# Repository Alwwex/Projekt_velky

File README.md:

# LaserPlan – chytrý laserový metr s Bluetooth pro náčrt půdorysu

Nakresli prstem nebo perem obrys místnosti na tabletu, ťukni na stěnu, zmáčkni **MĚŘIT** na laseru –
rozměr se sám zapíše do náčrtu, celý půdorys se přepočítá a aplikace vybere další stěnu.
Stěny, které jde dopočítat, měřit nemusíš. Na konci máš plochu, obvod a export do PNG / SVG / DXF.

| Deska plošného spoje (90 × 44 mm) | Spodní strana | Krabička pro 3D tisk |
|---|---|---|
|  |  |  |

## Co je v projektu

| Část | Kde | Stav |
|---|---|---|
| **Elektronika** – schéma, DPS (KiCad 7), Gerbery, kusovník, osazovací soubor | [`hardware/`](hardware/) | DRC bez chyb, 0 nespojených plošek |
| **Firmware** pro ESP32-C3 (Bluetooth LE, ovladače laser modulů, OLED, tlačítka, baterie) | [`firmware/`](firmware/) | přeloženo (PlatformIO) |
| **Aplikace** pro tablet/telefon/PC (náčrt půdorysu + Web Bluetooth), funguje offline | [`app/`](app/) | testy + E2E test v Chromiu prochází |
| **Krabička** pro 3D tisk (OpenSCAD + STL) | [`hardware/krabicka/`](hardware/krabicka/) | STL připravené |
| **Dokumentace** | [`docs/`](docs/) | |

## Jak to funguje

```mermaid
flowchart LR
  subgraph Přístroj["Laserový metr (ESP32-C3)"]
    L[Laserový modul<br/>UART] -->|vzdálenost| M[ESP32-C3]
    B[Tlačítko MĚŘIT] --> M
    M --> O[OLED displej]
    M --> Z[Bzučák]
    A[Li-Pol 1000 mAh<br/>nabíjení přes USB-C] --> M
  end
  M -- "Bluetooth LE<br/>(měření, stav, příkazy)" --> T
  subgraph T["Tablet / telefon / PC – aplikace v prohlížeči"]
    N[Náčrt perem → rovné stěny 90°/45°] --> S[Výběr stěny]
    S --> R[Přiřazení rozměru + dopočet<br/>uzavřeného obrysu]
    R --> E[Plocha, obvod, export PNG/SVG/DXF]
  end
```

1. **Laserový modul** (průmyslový UART dálkoměr, přesnost ±1–3 mm, dosah 40–100 m) změří vzdálenost.
2. **ESP32-C3** přičte offset podle zvolené reference (zadní / přední hrana krabičky), pípne, ukáže hodnotu
   na OLED a pošle ji přes **Bluetooth LE**.
3. **Aplikace** hodnotu zapíše do vybrané stěny. Náčrt se přeškáluje, „volné“ stěny se dopočítají tak,
   aby se obrys uzavřel, a jednoznačně určené stěny se označí `=` (ty měřit nemusíš).
   Když změříš všechno a obrys nesedí, aplikace ukáže **chybu uzavření** – víš, že je někde chyba.

## Rychlý start

### 1) Vyzkoušej aplikaci hned – bez hardwaru
```bash
cd app && python3 -m http.server 8000
# otevři http://localhost:8000 v Chrome/Edge → Připojit laser → Demo režim
```
Nebo zapni GitHub Pages (Settings → Pages → Source: **GitHub Actions**) – workflow
[`pages.yml`](.github/workflows/pages.yml) aplikaci nasadí na HTTPS adresu a přidá stránku pro nahrání firmwaru.

### 2) Prototyp bez vlastní desky (nejrychlejší cesta k fungujícímu měření)
ESP32-C3 SuperMini + laser modul + nepájivé pole → viz [docs/02-prototyp.md](docs/02-prototyp.md).

### 3) Plná verze s vlastní deskou a krabičkou
1. [Nákupní seznam](docs/01-nakupni-seznam.md) – co koupit a kde
2. [Výroba DPS](docs/03-vyroba-dps.md) – objednání desky (JLCPCB apod.), volitelně i s osazením
3. [Sestavení krok za krokem](docs/04-sestaveni.md) – pájení, oživení, laser, krabička, kalibrace
4. [Firmware](docs/05-firmware.md) – nahrání (i z prohlížeče), ovládání, sériová konzole
5. [Aplikace](docs/06-aplikace.md) – instalace na tablet, práce s náčrtem, export
6. [Bluetooth protokol](docs/07-ble-protokol.md) – pro vlastní aplikace

## Ovládání přístroje

| Tlačítko | Krátký stisk | Dlouhý stisk |
|---|---|---|
| **MĚŘIT** | 1. stisk zapne zaměřovací paprsek, 2. stisk měří | průběžné měření (SCAN) |
| **REŽIM** | reference: zadní ↔ přední hrana | jednotky m ↔ ft-in; 3 s = uspat |

Měřit jde i tlačítkem **MĚŘIT** v aplikaci. Modrá LED bliká = čeká na spojení, svítí = připojeno.
Červená LED = nabíjí se, zelená = nabito.

## Důležité poznámky

- **Hardware je navržený a zkontrolovaný softwarově, ale zatím nebyl fyzicky postaven a odzkoušen.**
  Deska prošla kontrolou DRC a netlist schématu je ověřený proti desce, firmware se přeloží a aplikace
  je otestovaná – první kus ale ber jako prototyp. Postup oživení s kontrolami je v [sestavení](docs/04-sestaveni.md).
- **Laserové moduly** se liší protokolem. Firmware umí binární protokol JRT a textový „D/O/C“
  protokol (automatická detekce) + simulaci. Před nákupem si ověř, že modul má **UART s logikou 3,3 V**.
- **iPad/iPhone**: Safari neumí Web Bluetooth – použij prohlížeč **Bluefy** (zdarma v App Store).
  Android, Windows, macOS, Linux a ChromeOS fungují v Chrome/Edge.
- **Li-Pol baterie**: zkontroluj polaritu konektoru (u čínských článků bývá opačně) – viz sestavení.

## Struktura repozitáře

```
app/                 webová aplikace (PWA, bez závislostí) + testy
firmware/            PlatformIO projekt pro ESP32-C3
hardware/
  generator/         Python skripty: zapojení → schéma → DPS → autorouter → výrobní data
  kicad/             KiCad 7 projekt (schéma, deska, knihovna symbolů)
  vyroba/            Gerbery (zip), BOM, CPL, schéma PDF, 3D model STEP
  krabicka/          OpenSCAD model + STL
docs/                návody a obrázky
```

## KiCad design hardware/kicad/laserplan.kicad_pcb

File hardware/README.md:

# Hardware LaserPlan

## Zapojení v kostce

| Blok | Součástky | Poznámka |
|---|---|---|
| USB-C | J1, R1/R2 (5,1 kΩ CC), U1 USBLC6-2SC6 | nabíjení + programování (nativní USB ESP32-C3), ESD ochrana |
| Nabíječka | U2 MCP73831 (≈ 450 mA, R3 2,2 kΩ), D2/D3 LED | červená = nabíjí, zelená = nabito |
| Napájecí cesta | D1 B5819W, Q1 AO3401A, R6 | z USB napájí systém přes diodu, baterie se automaticky odpojí (load sharing) |
| Vypínač, LDO | SW1, U3 AP2112K-3.3 (600 mA) | vypínač odpojí vše kromě nabíjení |
| Měření | R11/R12 (baterie → IO0), R13/R14 (USB → IO1) | |
| MCU | U4 ESP32-C3-WROOM-02 | anténa na hraně desky nad oblastí bez mědi |
| Laser | J2, Q2 AO3401A + Q3 AO3400A, JP1 | spínané napájení modulu s měkkým startem (C10), volba 3,3 V / baterie |
| Ovládání | SW2 MĚŘIT (= BOOT), SW3 REŽIM, D5 modrá LED, BZ1 + Q4 | |
| Displej | J3 – OLED SSD1306 I2C | |

### Piny ESP32-C3

| GPIO | Funkce | GPIO | Funkce |
|---|---|---|---|
| IO0 | ADC baterie | IO6 | I2C SCL |
| IO1 | detekce USB | IO7 | modrá LED |
| IO2 | laser AUX (strap, pull-up) | IO8 | strap (pull-up) |
| IO3 | laser EN | IO9 | MĚŘIT / BOOT |
| IO4 | REŽIM (probouzí ze spánku) | IO10 | bzučák |
| IO5 | I2C SDA | IO20 / IO21 | UART RX ← laser TX / TX → laser RX |
| IO18 / IO19 | USB D− / D+ | | |

## Jak návrh vznikl a jak ho upravit

Celý hardware je **generovaný z kódu** – jediným zdrojem pravdy je
[`generator/circuit.py`](generator/circuit.py) (součástky, hodnoty, pouzdra, sítě).

```bash
cd hardware/generator
./build_all.sh
```

| Skript | Co dělá |
|---|---|
| `gen_schematic.py` | schéma KiCad (`kicad/laserplan.kicad_sch`) – bloky, jmenovky sítí, vlastní symbol ESP32-C3-WROOM-02 |
| `gen_pcb.py place` | deska: footprinty z knihoven KiCadu, rozmístění (`PLACEMENT`), obrys, sítotisk |
| `router.py` | vlastní dvouvrstvý autorouter (A* na mřížce 0,25 mm s přesnou kontrolou izolací, rip-up & reroute, pevně navržené vyvedení USB-C) |
| `gen_pcb.py finish` | rozlitá zem na obou vrstvách, prošívací prokovy, DRC report |
| `export.py` | Gerbery, vrtání, BOM, CPL, PDF schéma, náhledy, STEP |

Potřebuješ **KiCad 7** (s Python modulem `pcbnew`), Python 3 s `numpy` a `cairosvg`.

Kontroly:
- `kicad/drc_report.txt` – **0 chyb, 0 nespojených plošek**. Jediná zbylá upozornění jsou
  `lib_footprint_issues` – vznikají jen proto, že v generovacím prostředí nebyla nastavená globální
  tabulka knihoven footprintů; v normálně nainstalovaném KiCadu zmizí.
- Netlist exportovaný ze schématu (`kicad-cli sch export netlist`) se shoduje s `circuit.py` (34 sítí).

> Pokud budeš desku dál upravovat ručně v KiCadu, už ji negeneruj skripty znovu (přepsaly by tvé změny).
> Schéma a deska jsou propojené (stejná UUID), takže *Aktualizovat DPS ze schématu* funguje.

## Rozměry

- DPS 90 × 44 mm, otvory M2.5 ve vzdálenosti 3,2 mm od rohů
- výška součástek nad DPS: tlačítka 13 mm, OLED na dutinkové liště ≈ 13,7 mm, bzučák 9,5 mm
- pod DPS jen vývody THT součástek (≈ 2 mm)
- krabička: 95 × 52 × 36 mm ([`krabicka/krabicka.scad`](krabicka/krabicka.scad))

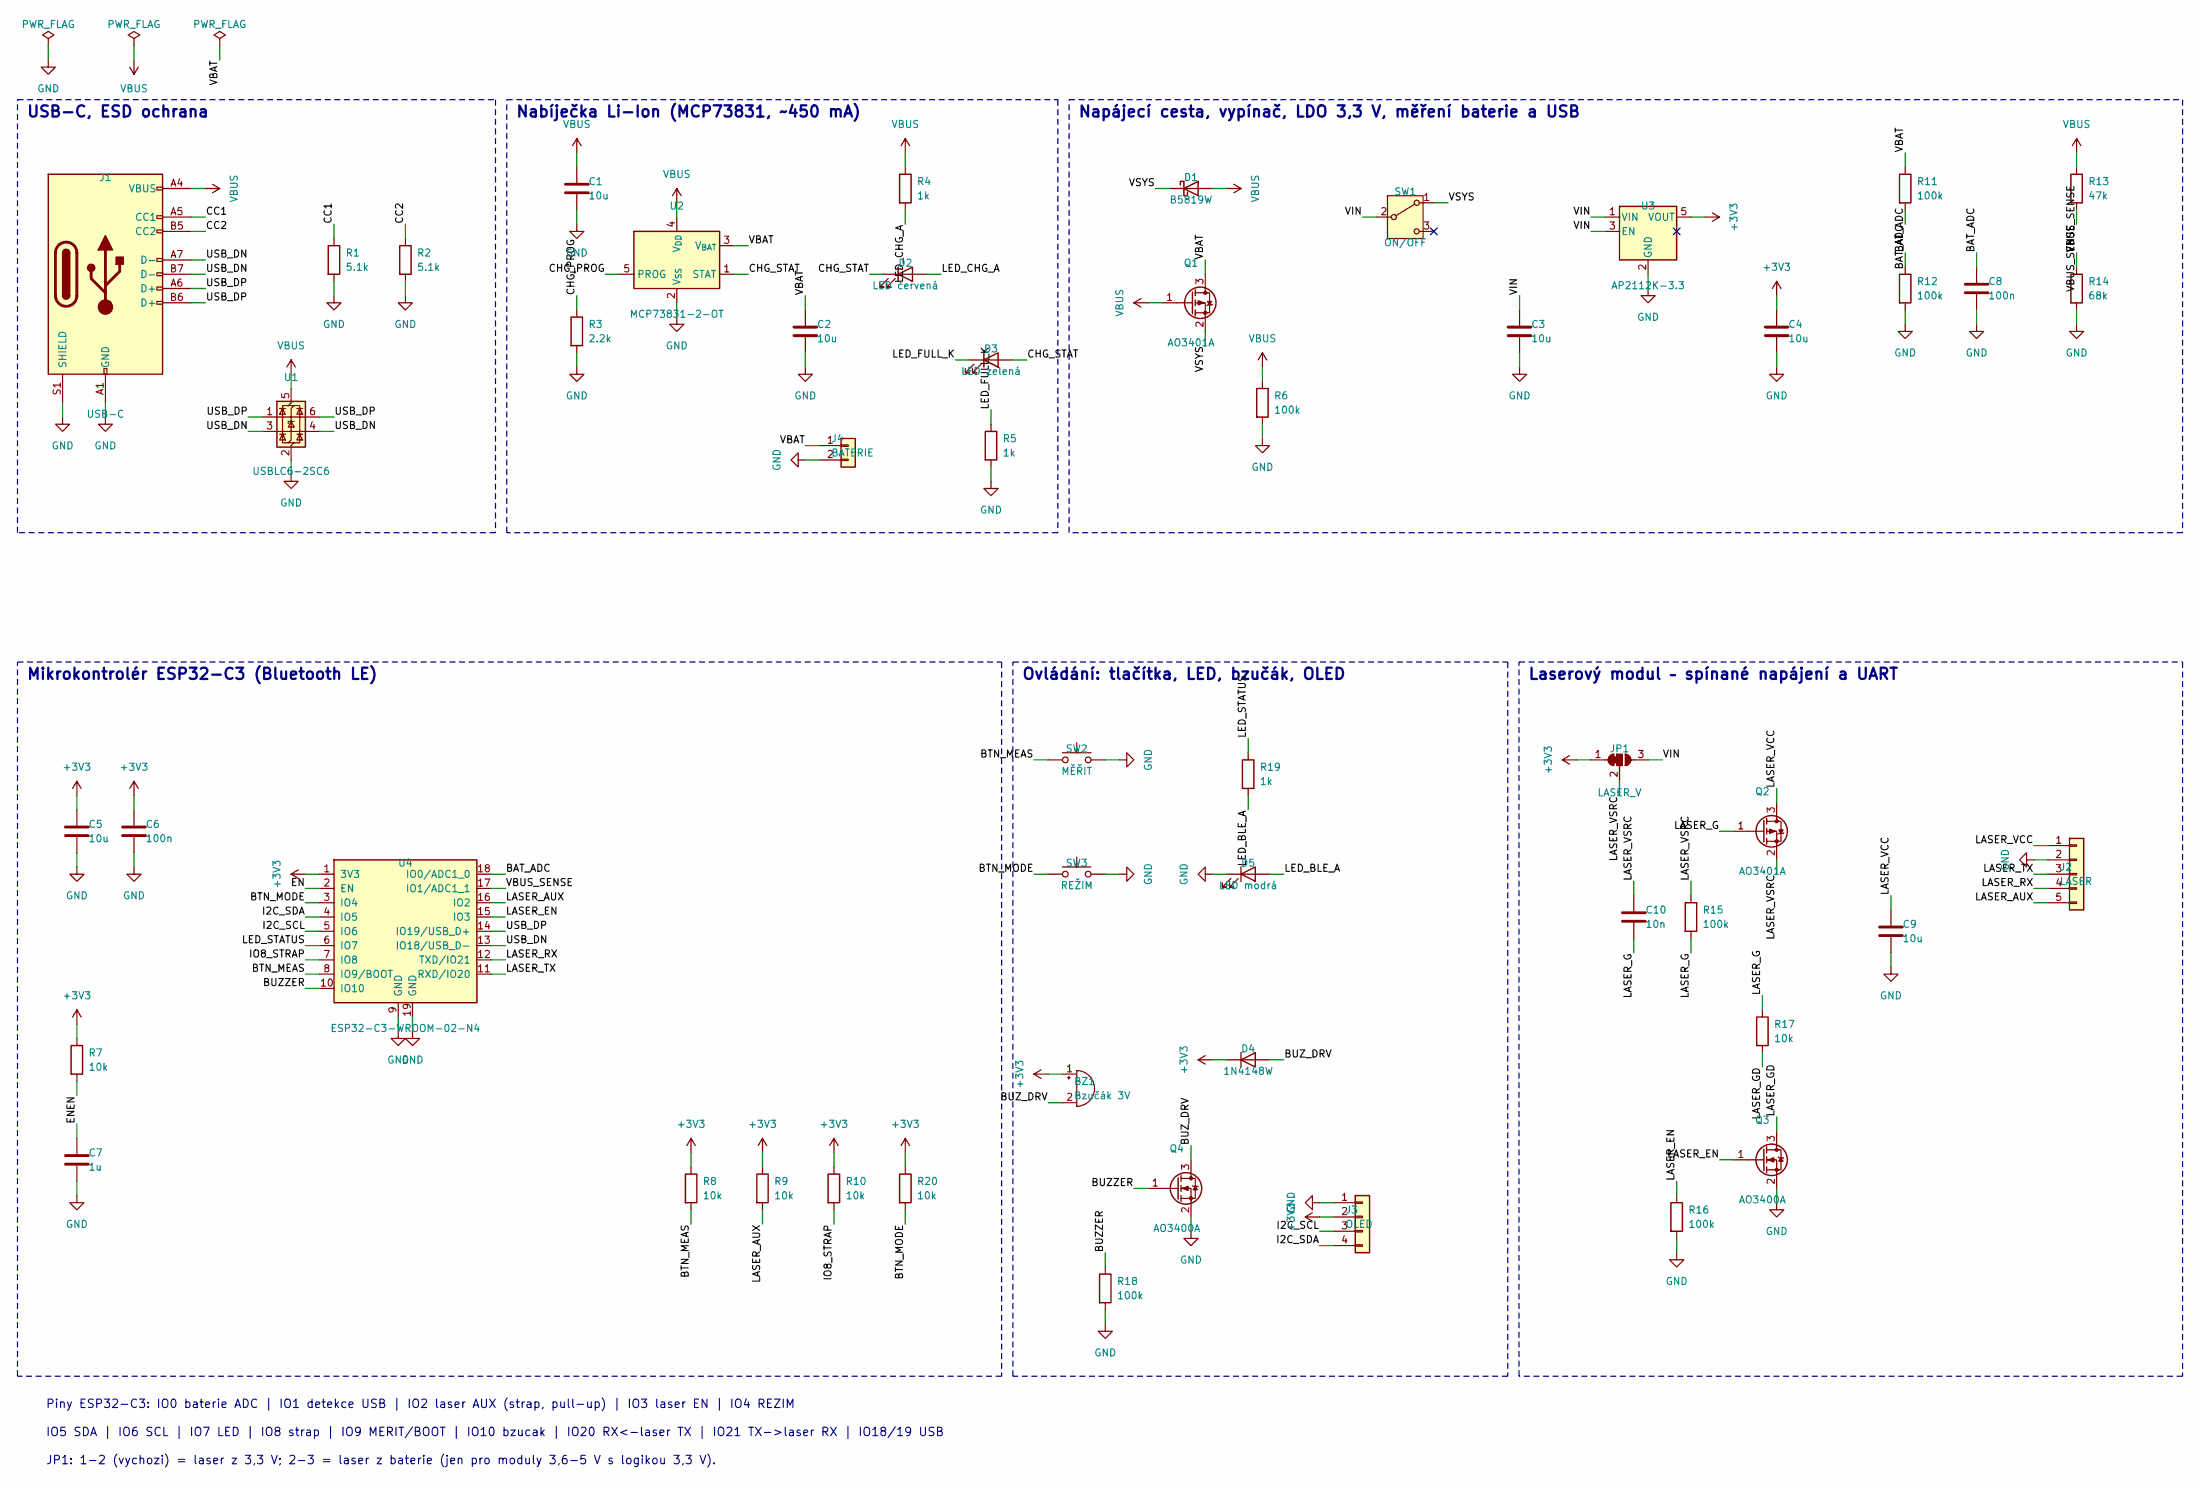
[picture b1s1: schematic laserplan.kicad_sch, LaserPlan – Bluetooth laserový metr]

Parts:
BZ1: Bzučák 3V; Buzzer_12x9.5RM7.6; MPN Pasivní magnetický bzučák 12×9,5 mm, 3 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
C1, C2, C3, C4, C5, C9: 10u; C_0805_2012Metric; MPN 0805 10u X5R/X7R ≥10V
C6, C8: 100n; C_0805_2012Metric; MPN 0805 100n X5R/X7R ≥10V
C7: 1u; C_0805_2012Metric; MPN 0805 1u X5R/X7R ≥10V
C10: 10n; C_0805_2012Metric; MPN 0805 10n X5R/X7R ≥10V
D1: B5819W; D_SOD-123; MPN B5819W
D2: LED červená; LED_0805_2012Metric; MPN LED 0805 červená
D3: LED zelená; LED_0805_2012Metric; MPN LED 0805 zelená
D4: 1N4148W; D_SOD-123; MPN 1N4148W
D5: LED modrá; LED_0805_2012Metric; MPN LED 0805 modrá
J1: USB-C; USB_C_Receptacle_HRO_TYPE-C-31-M-12; MPN TYPE-C-31-M-12
J2: LASER; PinHeader_1x05_P2.54mm_Vertical; MPN Kolíková lišta 1×5, 2,54 mm
J3: OLED; PinSocket_1x04_P2.54mm_Vertical; MPN Dutinková lišta 1×4, 2,54 mm
J4: BATERIE; JST_PH_B2B-PH-K_1x02_P2.00mm_Vertical; MPN B2B-PH-K-S
JP1: LASER_V; SolderJumper-3_P1.3mm_Bridged12_RoundedPad1.0x1.5mm; MPN (pájecí propojka na DPS)
Q1, Q2: AO3401A; SOT-23; MPN AO3401A
Q3, Q4: AO3400A; SOT-23; MPN AO3400A
R1, R2: 5.1k; R_0805_2012Metric; MPN 0805 5.1k 1%
R3: 2.2k; R_0805_2012Metric; MPN 0805 2.2k 1%
R4, R5, R19: 1k; R_0805_2012Metric; MPN 0805 1k 1%
R6, R11, R12, R15, R16, R18: 100k; R_0805_2012Metric; MPN 0805 100k 1%
R7, R8, R9, R10, R17, R20: 10k; R_0805_2012Metric; MPN 0805 10k 1%
R13: 47k; R_0805_2012Metric; MPN 0805 47k 1%
R14: 68k; R_0805_2012Metric; MPN 0805 68k 1%
SW1: ON/OFF; SW_Slide_SPDT_Angled_CK_OS102011MA1Q; MPN OS102011MA1QN1
SW2: MĚŘIT; SW_PUSH_6mm_H13mm; MPN TS-1187A / B3F-1070 (6×6 mm, výška 13 m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
SW3: REŽIM; SW_PUSH_6mm_H13mm; MPN TS-1187A / B3F-1070 (6×6 mm, výška 13 m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
U1: USBLC6-2SC6; SOT-23-6; MPN USBLC6-2SC6
U2: MCP73831-2-OT; SOT-23-5; MPN MCP73831T-2ACI/OT
U3: AP2112K-3.3; SOT-23-5; MPN AP2112K-3.3TRG1
U4: ESP32-C3-WROOM-02-N4; ESP32-C3-WROOM-02; MPN ESP32-C3-WROOM-02-N4

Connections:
+3V3: BZ1.1 (+), C4.1, C5.1, C6.1, D4.1 (K), J3.2, JP1.1 (A), R7.1, R8.1, R9.1, R10.1, R20.1, U3.5 (VOUT), U4.1 (3V3)
BAT_ADC: C8.1, R11.2, R12.1, U4.18 (IO0/ADC1_0)
BTN_MEAS: R8.2, SW2.1, U4.8 (IO9/BOOT)
BTN_MODE: R20.2, SW3.1, U4.3 (IO4)
BUZZER: Q4.1 (G), R18.1, U4.10 (IO10)
BUZ_DRV: BZ1.2 (-), D4.2 (A), Q4.3 (D)
CC1: J1.A5 (CC1), R1.1
CC2: J1.B5 (CC2), R2.1
CHG_PROG: R3.1, U2.5 (PROG)
CHG_STAT: D2.1 (K), D3.2 (A), U2.1 (STAT)
EN: C7.1, R7.2, U4.2 (EN)
GND: C1.2, C2.2, C3.2, C4.2, C5.2, C6.2, C7.2, C8.2, C9.2, D5.1 (K), J1.A1 (GND), J1.A12 (GND), J1.B1 (GND), J1.B12 (GND), J1.S1 (SHIELD), J2.2, J3.1, J4.2, Q3.2 (S), Q4.2 (S), R1.2, R2.2, R3.2, R5.2, R6.2, R12.2, R14.2, R16.2, R18.2, SW2.2, SW3.2, U1.2 (GND), U2.2 (V_{SS}), U3.2 (GND), U4.9 (GND), U4.19 (GND)
I2C_SCL: J3.3, U4.5 (IO6)
I2C_SDA: J3.4, U4.4 (IO5)
IO8_STRAP: R10.2, U4.7 (IO8)
LASER_AUX: J2.5, R9.2, U4.16 (IO2)
LASER_EN: Q3.1 (G), R16.1, U4.15 (IO3)
LASER_G: C10.2, Q2.1 (G), R15.2, R17.1
LASER_GD: Q3.3 (D), R17.2
LASER_RX: J2.4, U4.12 (TXD/IO21)
LASER_TX: J2.3, U4.11 (RXD/IO20)
LASER_VCC: C9.1, J2.1, Q2.3 (D)
LASER_VSRC: C10.1, JP1.2 (C), Q2.2 (S), R15.1
LED_BLE_A: D5.2 (A), R19.2
LED_CHG_A: D2.2 (A), R4.2
LED_FULL_K: D3.1 (K), R5.1
LED_STATUS: R19.1, U4.6 (IO7)
USB_DN: J1.A7 (D-), J1.B7 (D-), U1.3 (I/O2), U1.4 (I/O2), U4.13 (IO18/USB_D-)
USB_DP: J1.A6 (D+), J1.B6 (D+), U1.1 (I/O1), U1.6 (I/O1), U4.14 (IO19/USB_D+)
VBAT: C2.1, J4.1, Q1.3 (D), R11.1, U2.3 (V_{BAT})
VBUS: C1.1, D1.2 (A), J1.A4 (VBUS), J1.A9 (VBUS), J1.B4 (VBUS), J1.B9 (VBUS), Q1.1 (G), R4.1, R6.1, R13.1, U1.5 (VBUS), U2.4 (V_{DD})
VBUS_SENSE: R13.2, R14.1, U4.17 (IO1/ADC1_1)
VIN: C3.1, JP1.3 (B), SW1.2 (B), U3.1 (VIN), U3.3 (EN)
VSYS: D1.1 (K), Q1.2 (S), SW1.1 (A)

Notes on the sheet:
USB-C, ESD ochrana
Nabíječka Li-Ion (MCP73831, ~450 mA)
Napájecí cesta, vypínač, LDO 3,3 V, měření baterie a USB
Mikrokontrolér ESP32-C3 (Bluetooth LE)
Ovládání: tlačítka, LED, bzučák, OLED
Laserový modul – spínané napájení a UART
Piny ESP32-C3: IO0 baterie ADC | IO1 detekce USB | IO2 laser AUX (strap, pull-up) | IO3 laser EN | IO4 REZIM
IO5 SDA | IO6 SCL | IO7 LED | IO8 strap | IO9 MERIT/BOOT | IO10 bzucak | IO20 RX<-laser TX | IO21 TX->laser RX | IO18/19 USB
JP1: 1-2 (vychozi) = laser z 3,3 V; 2-3 = laser z baterie (jen pro moduly 3,6-5 V s logikou 3,3 V).

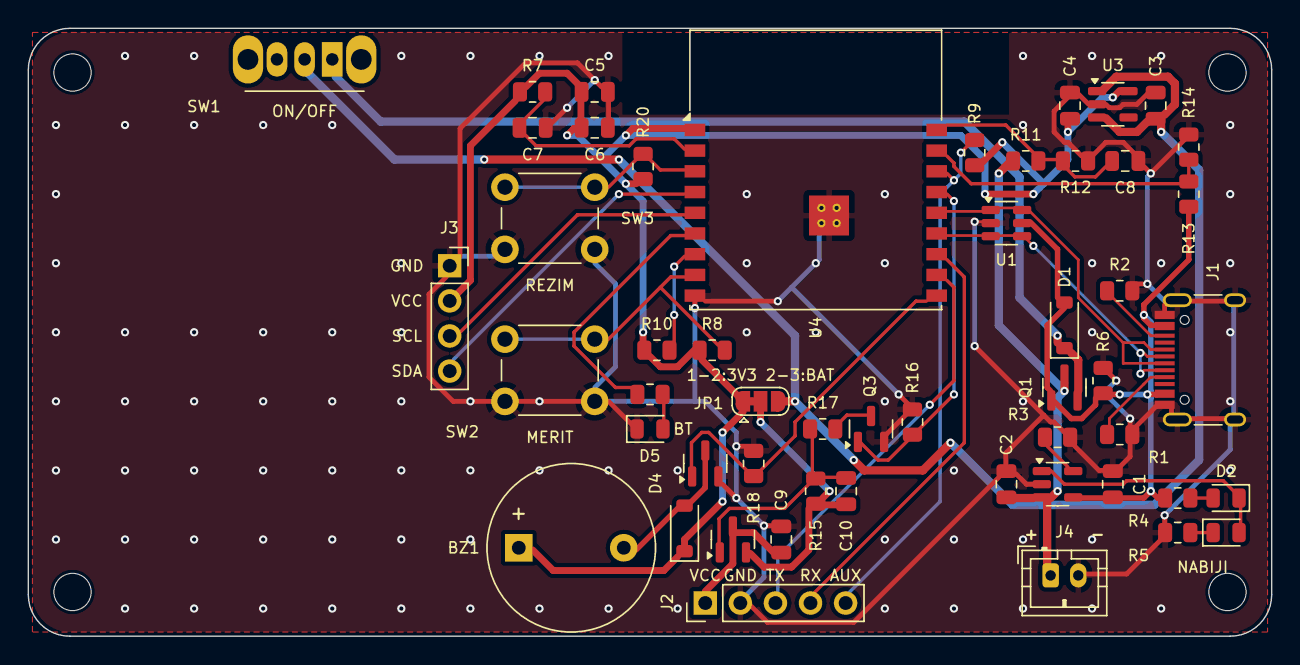
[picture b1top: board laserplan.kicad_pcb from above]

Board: 2 copper layers, 90.0 x 44.0 mm, 56 parts (0 on the bottom side), 34 nets.

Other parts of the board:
H1, H2, H3, H4: M2.5; MountingHole_2.7mm_M2.5

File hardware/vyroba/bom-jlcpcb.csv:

Comment,Designator,Footprint,LCSC Part #,MPN
10u,"C1,C2,C3,C4,C5,C9",C_0805_2012Metric,,0805 10u X5R/X7R ≥10V
10n,C10,C_0805_2012Metric,,0805 10n X5R/X7R ≥10V
100n,"C6,C8",C_0805_2012Metric,,0805 100n X5R/X7R ≥10V
1u,C7,C_0805_2012Metric,,0805 1u X5R/X7R ≥10V
B5819W,D1,D_SOD-123,,B5819W
LED červená,D2,LED_0805_2012Metric,,LED 0805 červená
LED zelená,D3,LED_0805_2012Metric,,LED 0805 zelená
1N4148W,D4,D_SOD-123,,1N4148W
LED modrá,D5,LED_0805_2012Metric,,LED 0805 modrá
USB-C,J1,USB_C_Receptacle_HRO_TYPE-C-31-M-12,,TYPE-C-31-M-12
AO3401A,"Q1,Q2",SOT-23,,AO3401A
AO3400A,"Q3,Q4",SOT-23,,AO3400A
5.1k,"R1,R2",R_0805_2012Metric,,0805 5.1k 1%
47k,R13,R_0805_2012Metric,,0805 47k 1%
68k,R14,R_0805_2012Metric,,0805 68k 1%
2.2k,R3,R_0805_2012Metric,,0805 2.2k 1%
1k,"R4,R5,R19",R_0805_2012Metric,,0805 1k 1%
100k,"R6,R11,R12,R15,R16,R18",R_0805_2012Metric,,0805 100k 1%
10k,"R7,R8,R9,R10,R17,R20",R_0805_2012Metric,,0805 10k 1%
USBLC6-2SC6,U1,SOT-23-6,,USBLC6-2SC6
MCP73831-2-OT,U2,SOT-23-5,,MCP73831T-2ACI/OT
AP2112K-3.3,U3,SOT-23-5,,AP2112K-3.3TRG1
ESP32-C3-WROOM-02-N4,U4,ESP32-C3-WROOM-02,,ESP32-C3-WROOM-02-N4

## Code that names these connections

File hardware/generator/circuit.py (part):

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    dict(ref="U1", symbol="Power_Protection:USBLC6-2SC6", value="USBLC6-2SC6",
         footprint=SOT236, manufacturer="STMicroelectronics", mpn="USBLC6-2SC6",
         desc="ESD ochrana USB datových linek", block="usb", smd=True,
         pins={"1": "USB_DP", "6": "USB_DP", "3": "USB_DN", "4": "USB_DN",
               "2": "GND", "5": "VBUS"}),

    # ---------------------------------------------------------------- nabíječka Li-Ion
    dict(ref="U2", symbol="Battery_Management:MCP73831-2-OT", value="MCP73831-2-OT",
         footprint=SOT235, manufacturer="Microchip", mpn="MCP73831T-2ACI/OT",
         desc="Nabíječka 1článku Li-Ion/LiPo 4,2 V", block="charger", smd=True,
         pins={"1": "CHG_STAT", "2": "GND", "3": "VBAT", "4": "VBUS", "5": "CHG_PROG"}),
    R("R3", "2.2k", "CHG_PROG", "GND", "charger", "Nabíjecí proud ≈ 450 mA (1000/R)"),
    C("C1", "10u", "VBUS", "GND", "charger", "Vstupní kondenzátor nabíječky"),
    C("C2", "10u", "VBAT", "GND", "charger", "Výstupní kondenzátor nabíječky"),
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    dict(ref="D1", symbol="Device:D_Schottky", value="B5819W",
         footprint=SOD123, manufacturer="Diodes / SL", mpn="B5819W",
         desc="Schottky – napájení z USB", block="power", smd=True,
         pins={"1": "VSYS", "2": "VBUS"}),           # 1 = K, 2 = A
    dict(ref="Q1", symbol="Transistor_FET:AO3401A", value="AO3401A",
         footprint=SOT23, manufacturer="Alpha & Omega", mpn="AO3401A",
         desc="P-MOSFET – přepínání baterie/USB (load sharing)", block="power", smd=True,
         pins={"1": "VBUS", "2": "VSYS", "3": "VBAT"}),  # G, S, D
    R("R6", "100k", "VBUS", "GND", "power", "Stahuje gate Q1 bez USB"),
    dict(ref="SW1", symbol="Switch:SW_SPDT", value="ON/OFF",
         footprint="Button_Switch_THT:SW_Slide_SPDT_Angled_CK_OS102011MA1Q",
         manufacturer="C&K", mpn="OS102011MA1QN1",
         desc="Hlavní vypínač (posuvný, úhlový – ovládá se z boku krabičky)", block="power", smd=False,
         pins={"1": "VSYS", "2": "VIN", "3": "NC_SW1"}),
    C("C3", "10u", "VIN", "GND", "power", "Vstup LDO"),
    dict(ref="U3", symbol="Regulator_Linear:AP2112K-3.3", value="AP2112K-3.3",
         footprint=SOT235, manufacturer="Diodes Inc.", mpn="AP2112K-3.3TRG1",
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         # IO4 REŽIM | IO5 SDA | IO6 SCL | IO7 LED | IO8 strap | IO9 MĚŘIT/BOOT
         # IO10 bzučák | IO20 RX<-laser | IO21 TX->laser | IO18/19 USB
         # IO3 laser EN | IO2 laser AUX | IO1 detekce USB | IO0 baterie (ADC)
         pins={"1": "+3V3", "2": "EN", "3": "BTN_MODE", "4": "I2C_SDA",
               "5": "I2C_SCL", "6": "LED_STATUS", "7": "IO8_STRAP", "8": "BTN_MEAS",
               "9": "GND", "10": "BUZZER", "11": "LASER_TX", "12": "LASER_RX",
               "13": "USB_DN", "14": "USB_DP", "15": "LASER_EN", "16": "LASER_AUX",
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         footprint="Button_Switch_THT:SW_PUSH_6mm_H13mm", manufacturer="XKB / Omron",
         mpn="TS-1187A / B3F-1070 (6×6 mm, výška 13 mm)",
         desc="Tlačítko MĚŘIT (zároveň BOOT)", block="ui", smd=False,
         pins={"1": "BTN_MEAS", "2": "GND"}),
    dict(ref="SW3", symbol="Switch:SW_Push", value="REŽIM",
         footprint="Button_Switch_THT:SW_PUSH_6mm_H13mm", manufacturer="XKB / Omron",
         mpn="TS-1187A / B3F-1070 (6×6 mm, výška 13 mm)",
         desc="Tlačítko REŽIM / laser zap", block="ui", smd=False,
         pins={"1": "BTN_MODE", "2": "GND"}),
    R("R19", "1k", "LED_STATUS", "LED_BLE_A", "ui", "Rezistor stavové LED"),
    LED("D5", "modrá", "LED_BLE_A", "GND", "ui", "Stav Bluetooth"),

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         footprint="Buzzer_Beeper:Buzzer_12x9.5RM7.6", manufacturer="Generic",
         mpn="Pasivní magnetický bzučák 12×9,5 mm, 3 V (např. HYT-1205)",
         desc="Akustická signalizace měření", block="ui", smd=False,
         pins={"1": "+3V3", "2": "BUZ_DRV"}),
    dict(ref="Q4", symbol="Transistor_FET:AO3400A", value="AO3400A",
         footprint=SOT23, manufacturer="Alpha & Omega", mpn="AO3400A",
         desc="Spínač bzučáku", block="ui", smd=True,
         pins={"1": "BUZZER", "2": "GND", "3": "BUZ_DRV"}),
    R("R18", "100k", "BUZZER", "GND", "ui", "Gate pull-down"),
    dict(ref="D4", symbol="Device:D", value="1N4148W",
         footprint=SOD123, manufacturer="Diodes / SL", mpn="1N4148W",
         desc="Ochranná dioda bzučáku", block="ui", smd=True,
         pins={"1": "+3V3", "2": "BUZ_DRV"}),         # K, A

    # ---------------------------------------------------------------- laser modul
    dict(ref="JP1", symbol="Jumper:SolderJumper_3_Bridged12", value="LASER_V",
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         manufacturer="-", mpn="(pájecí propojka na DPS)",
         desc="Volba napájení laseru: 1-2 = 3,3 V (výchozí), 2-3 = baterie", block="laser",
         smd=True, no_bom=True,
         pins={"1": "+3V3", "2": "LASER_VSRC", "3": "VIN"}),
    dict(ref="Q2", symbol="Transistor_FET:AO3401A", value="AO3401A",
         footprint=SOT23, manufacturer="Alpha & Omega", mpn="AO3401A",
         desc="Spínač napájení laser modulu", block="laser", smd=True,
         pins={"1": "LASER_G", "2": "LASER_VSRC", "3": "LASER_VCC"}),
    R("R15", "100k", "LASER_VSRC", "LASER_G", "laser", "Gate pull-up (laser vyp.)"),
    C("C10", "10n", "LASER_VSRC", "LASER_G", "laser", "Měkký start laseru"),
    R("R17", "10k", "LASER_G", "LASER_GD", "laser", "Omezení rychlosti sepnutí"),
    dict(ref="Q3", symbol="Transistor_FET:AO3400A", value="AO3400A",
         footprint=SOT23, manufacturer="Alpha & Omega", mpn="AO3400A",
         desc="Budič spínače laseru", block="laser", smd=True,
         pins={"1": "LASER_EN", "2": "GND", "3": "LASER_GD"}),
    R("R16", "100k", "LASER_EN", "GND", "laser", "Laser vypnutý po resetu"),
    C("C9", "10u", "LASER_VCC", "GND", "laser", "Blokování napájení laseru"),
    dict(ref="J2", symbol="Connector_Generic:Conn_01x05", value="LASER",
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         manufacturer="Generic", mpn="Kolíková lišta 1×5, 2,54 mm",
         desc="Laser modul: 1 VCC, 2 GND, 3 TX modulu, 4 RX modulu, 5 AUX", block="laser",
         smd=False,
         pins={"1": "LASER_VCC", "2": "GND", "3": "LASER_TX", "4": "LASER_RX", "5": "LASER_AUX"}),

    # ---------------------------------------------------------------- displej
    dict(ref="J3", symbol="Connector_Generic:Conn_01x04", value="OLED",
         footprint="Connector_PinSocket_2.54mm:PinSocket_1x04_P2.54mm_Vertical",
         manufacturer="Generic", mpn="Dutinková lišta 1×4, 2,54 mm",
         desc="OLED 0,96\" SSD1306 I2C: GND, VCC, SCL, SDA", block="ui", smd=False,
         pins={"1": "GND", "2": "+3V3", "3": "I2C_SCL", "4": "I2C_SDA"}),
]

# Díry pro šrouby M2.5 (jen na DPS, ne ve schématu)
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
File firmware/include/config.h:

#pragma once
// ============================================================================
//  LaserPlan – konfigurace pinů a výchozích hodnot
// ============================================================================
#include <Arduino.h>

#define LP_FW_VERSION "1.0.0"
#define LP_MODEL      "LaserPlan BLE"

// ---------------------------------------------------------------- piny
// Stejné zapojení platí pro vlastní DPS i pro ESP32-C3 SuperMini/DevKitM-1.
static constexpr int PIN_BAT_ADC    = 0;   // dělič 100k/100k z baterie (ADC1_CH0)
static constexpr int PIN_VBUS_SENSE = 1;   // dělič 47k/68k z USB 5 V
static constexpr int PIN_LASER_AUX  = 2;   // volitelný pin modulu (PWR/EN), strap – pull-up
static constexpr int PIN_LASER_EN   = 3;   // 1 = napájení laser modulu zapnuto
static constexpr int PIN_BTN_MODE   = 4;   // tlačítko REŽIM (aktivní v nule, budí z režimu spánku)
static constexpr int PIN_I2C_SDA    = 5;   // OLED
static constexpr int PIN_I2C_SCL    = 6;   // OLED
static constexpr int PIN_BUZZER     = 10;  // pasivní bzučák přes MOSFET
static constexpr int PIN_BTN_MEAS   = 9;   // tlačítko MĚŘIT (= BOOT)
static constexpr int PIN_LASER_RX   = 20;  // ESP RX  <- TX modulu
static constexpr int PIN_LASER_TX   = 21;  // ESP TX  -> RX modulu

#if defined(LP_BOARD_DEVKIT)
static constexpr int  PIN_LED        = 8;     // modrá LED na SuperMini
static constexpr bool LED_ACTIVE_LOW = true;
#else
static constexpr int  PIN_LED        = 7;     // modrá LED "BT" na DPS
static constexpr bool LED_ACTIVE_LOW = false;
#endif

// ---------------------------------------------------------------- laser
// Typ modulu: 0 = automatická detekce, 1 = JRT binární protokol,
//             2 = ASCII protokol ("D"/"O"/"C"), 3 = simulace (bez modulu)
static constexpr uint8_t LASER_DRIVER_DEFAULT = 0;

// Vzdálenost (mm) od nulového bodu modulu k ZADNÍ hraně krabičky.
// Přesně se nastaví kalibrací v aplikaci (Nastavení -> Kalibrace).
static constexpr float REAR_OFFSET_MM_DEFAULT  = 93.0f;   // krabicka.scad: 93 mm
// Korekce pro měření od PŘEDNÍ hrany (obvykle 0).
static constexpr float FRONT_OFFSET_MM_DEFAULT = -2.0f;  // přední stěna 2 mm

static constexpr uint32_t LASER_MEASURE_TIMEOUT_MS = 4000;
static constexpr uint32_t LASER_POINTER_TIMEOUT_MS = 30000;  // zaměřovací paprsek
static constexpr uint32_t LASER_IDLE_POWER_OFF_MS  = 60000;  // vypnout modul

// ---------------------------------------------------------------- napájení
static constexpr float    BAT_DIVIDER          = 2.0f;     // 100k/100k
static constexpr uint32_t SLEEP_AFTER_MS       = 10UL * 60UL * 1000UL;  // 10 min
static constexpr uint32_t STATUS_PERIOD_MS     = 5000;

// ---------------------------------------------------------------- OLED
// Na DPS je záhlaví OLED směrem DOZADU (k uživateli), proto je obraz
// otočený o 180° (hodnota 2). Pokud máš text vzhůru nohama, dej 0.
static constexpr uint8_t OLED_ROTATION = 2;
static constexpr uint8_t OLED_I2C_ADDR = 0x3C;

// ---------------------------------------------------------------- BLE
// Vlastní služba "LaserPlan" (viz docs/ble-protokol.md)
#define LP_SERVICE_UUID     "4c500001-6c61-7365-7270-6c616e000000"
#define LP_MEASUREMENT_UUID "4c500002-6c61-7365-7270-6c616e000000"
#define LP_CONTROL_UUID     "4c500003-6c61-7365-7270-6c616e000000"
#define LP_STATUS_UUID      "4c500004-6c61-7365-7270-6c616e000000"
